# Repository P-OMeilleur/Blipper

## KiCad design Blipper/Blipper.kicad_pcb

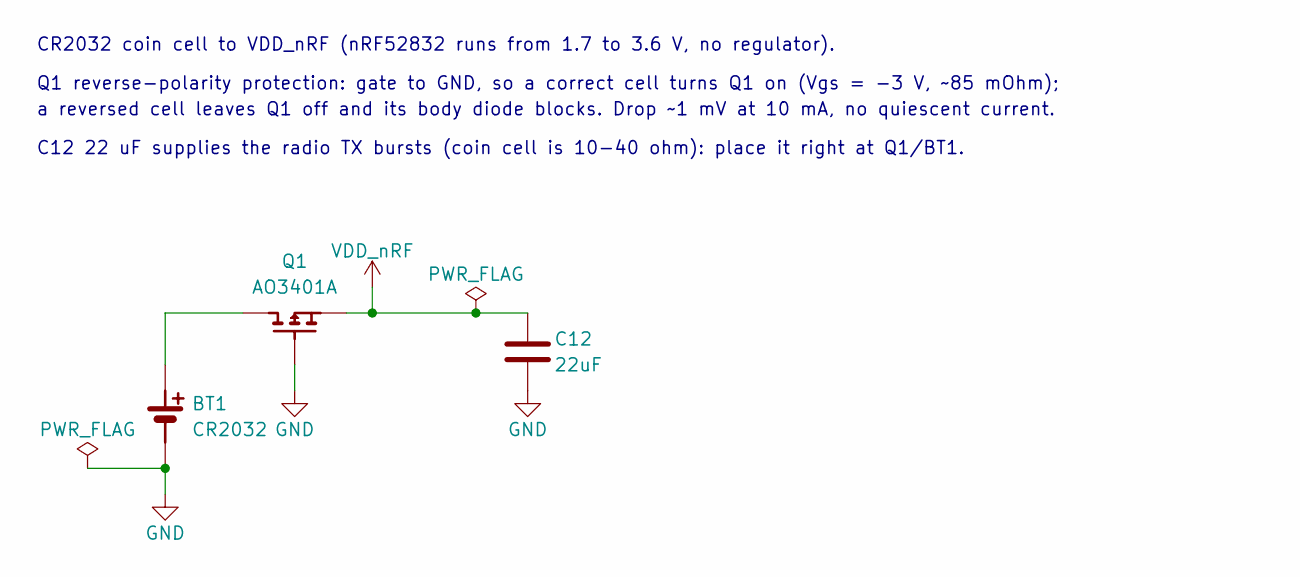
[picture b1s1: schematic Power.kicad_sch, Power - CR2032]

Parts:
BT1: CR2032; BatteryHolder_MYOUNG_MY-2032-16; MPN MY-2032-16; LCSC C2902340
C12: 22uF; C_0603_1608Metric; MPN CL10A226MQ8NRNC; LCSC C59461
Q1: AO3401A; SOT-23; MPN AO3401A; LCSC C15127

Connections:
GND: BT1.2 (-), C12.2, Q1.1 (G); also elsewhere on the board
unnamed: BT1.1 (+), Q1.3 (D)
VDD_nRF: C12.1, Q1.2 (S); also elsewhere on the board

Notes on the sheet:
C12 22 uF supplies the radio TX bursts (coin cell is 10-40 ohm): place it right at Q1/BT1.
Q1 reverse-polarity protection: gate to GND, so a correct cell turns Q1 on (Vgs = -3 V, ~85 mOhm);
CR2032 coin cell to VDD_nRF (nRF52832 runs from 1.7 to 3.6 V, no regulator).
a reversed cell leaves Q1 off and its body diode blocks. Drop ~1 mV at 10 mA, no quiescent current.

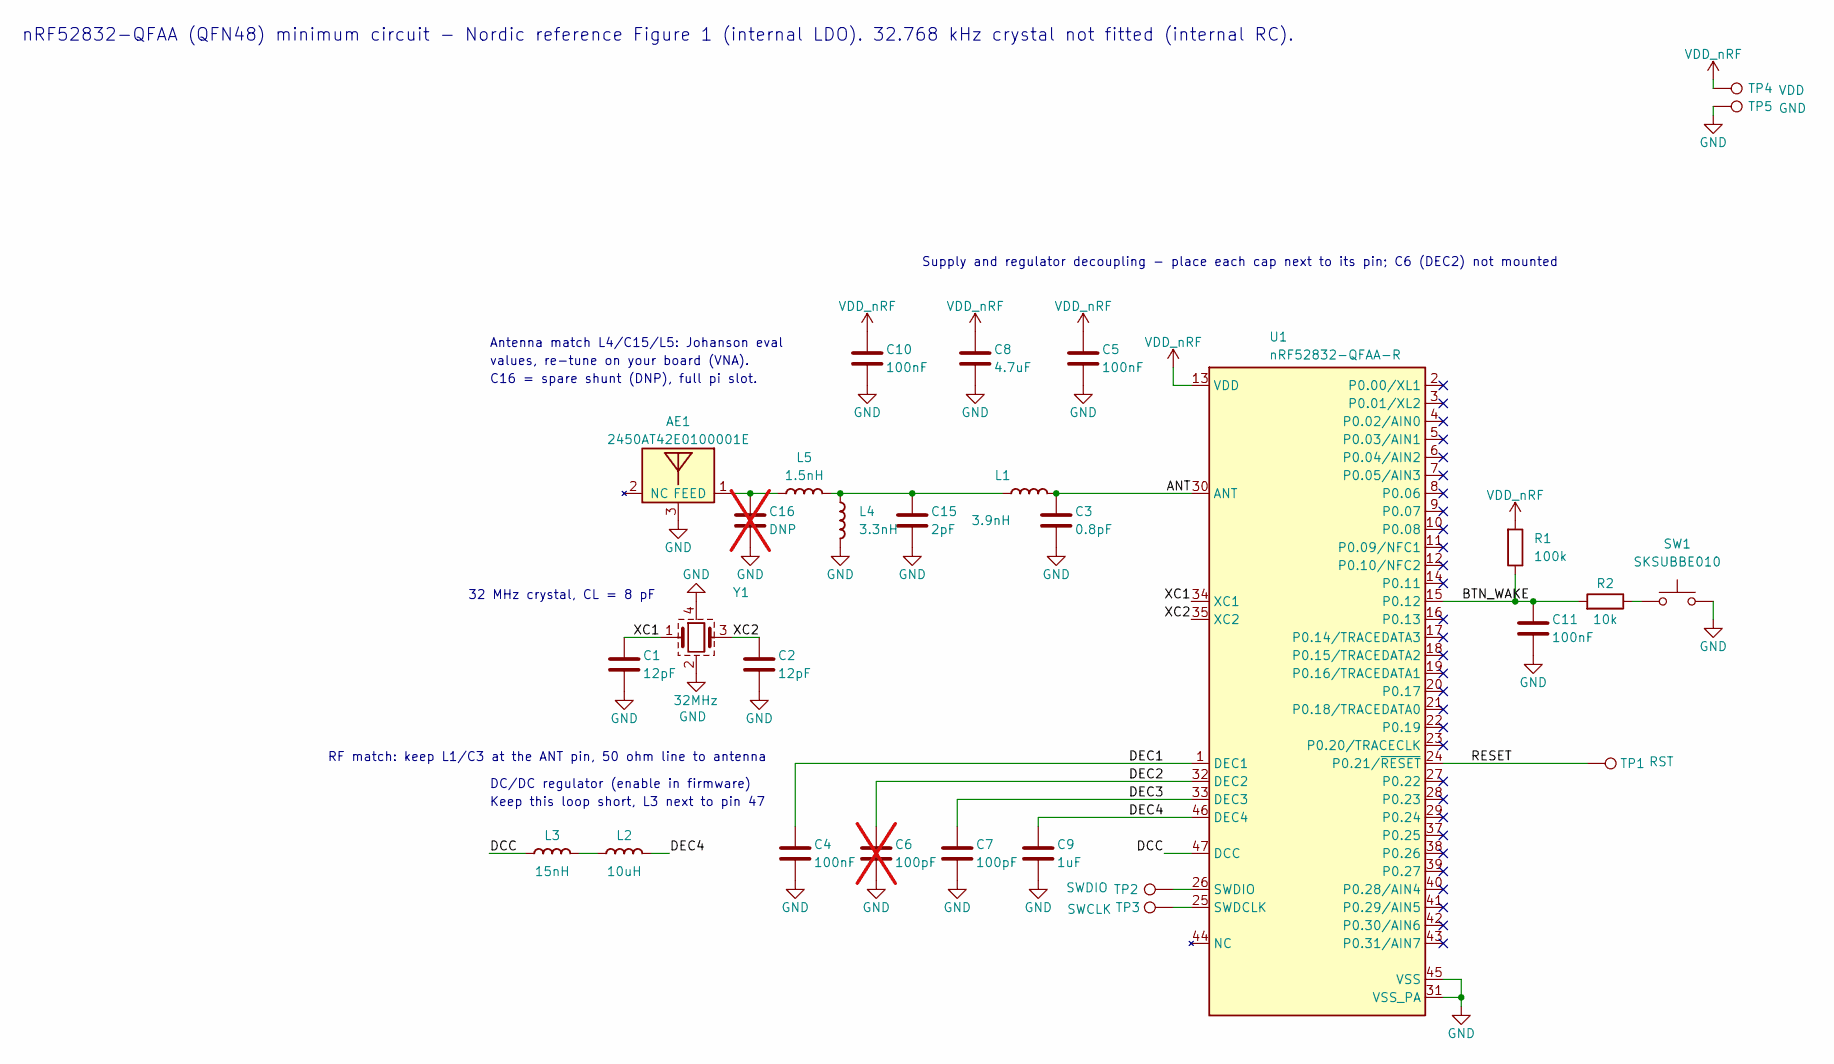
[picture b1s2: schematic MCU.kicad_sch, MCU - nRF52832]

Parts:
AE1: 2450AT42E0100001E; Antenna_Johanson_2450AT42E0100; MPN 2450AT42E0100001E; LCSC C17605137
C1, C2: 12pF; C_0402_1005Metric; MPN GRM1555C1H120GA01D; LCSC C161527
C3: 0.8pF; C_0402_1005Metric; MPN GJM1555C1HR80WB01D; LCSC C88902
C4, C5, C10, C11: 100nF; C_0402_1005Metric; MPN CL05B104KO5NNNC; LCSC C1525
C6: 100pF; C_0402_1005Metric; MPN 0402CG101J500NT; LCSC C1546; not fitted
C7: 100pF; C_0402_1005Metric; MPN 0402CG101J500NT; LCSC C1546
C8: 4.7uF; C_0603_1608Metric; MPN CL10A475KO8NNNC; LCSC C19666
C9: 1uF; C_0603_1608Metric; MPN CL10B105KA8NNNC; LCSC C29936
C15: 2pF; C_0402_1005Metric; MPN GJM1555C1H2R0BB01D; LCSC C161316
C16: DNP; C_0402_1005Metric; MPN GJM1555C1H2R0BB01D; LCSC C161316; not fitted
L1: 3.9nH; L_0402_1005Metric; MPN LQG15HS3N9S02D; LCSC C77109
L2: 10uH; L_0603_1608Metric; MPN MLZ1608M100WT000; LCSC C76798
L3: 15nH; L_0402_1005Metric; MPN VHF100505HQ15NJT; LCSC C395049
L4: 3.3nH; L_0402_1005Metric; MPN LQG15HS3N3S02D; LCSC C86064
L5: 1.5nH; L_0402_1005Metric; MPN LQG15HS1N5S02D; LCSC C77106
R1: 100k; R_0402_1005Metric; MPN 0402WGF1003TCE; LCSC C25741
R2: 10k; R_0402_1005Metric; MPN 0402WGF1002TCE; LCSC C25744
SW1: SKSUBBE010; SW_Alps_SKSU_5.4x5.3mm; MPN SKSUBBE010; LCSC C726003
TP1: RST; TestPoint_THTPad_D1.36mm_Drill1.0mm
TP2: SWDIO; TestPoint_THTPad_D1.36mm_Drill1.0mm
TP3: SWCLK; TestPoint_THTPad_D1.36mm_Drill1.0mm
TP4: VDD; TestPoint_THTPad_D1.36mm_Drill1.0mm
TP5: GND; TestPoint_THTPad_D1.36mm_Drill1.0mm
U1: nRF52832-QFAA-R; Nordic_QFN-48-1EP_6x6mm_P0.4mm_EP4.6x4.6mm
Y1: 32MHz; Crystal_SMD_2016-4Pin_2.0x1.6mm; MPN TX201632M4BBCE2T; LCSC C5339095

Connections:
/MCU/ANT: C3.1, L1.2, U1.30 (ANT)
/MCU/BTN_WAKE: C11.1, R1.2, R2.1, U1.15 (P0.12)
/MCU/DCC: L3.1, U1.47 (DCC)
/MCU/DEC1: C4.1, U1.1 (DEC1)
/MCU/DEC2: C6.1, U1.32 (DEC2)
/MCU/DEC3: C7.1, U1.33 (DEC3)
/MCU/DEC4: C9.1, L2.2, U1.46 (DEC4)
/MCU/RESET: TP1.1 (1_1), U1.24 (P0.21/~RESET)
/MCU/XC1: C1.1, U1.34 (XC1), Y1.1
/MCU/XC2: C2.1, U1.35 (XC2), Y1.3
GND: AE1.3, AE1.4, C1.2, C2.2, C3.2, C4.2, C5.2, C6.2, C7.2, C8.2, C9.2, C10.2, C11.2, C15.2, C16.2, L4.2, SW1.2, TP5.1 (1_1), U1.31 (VSS_PA), U1.45 (VSS), U1.49 (VSS), Y1.2 (GND), Y1.4 (GND); also elsewhere on the board
unnamed: AE1.1 (FEED_1), C16.1, L5.1
unnamed: C15.1, L1.1, L4.1, L5.2
unnamed: L2.1, L3.2
unnamed: R2.2, SW1.1
unnamed: TP3.1 (1_1), U1.25 (SWDCLK)
unnamed: TP2.1 (1_1), U1.26 (SWDIO)
VDD_nRF: C5.1, C8.1, C10.1, R1.1, TP4.1 (1_1), U1.13 (VDD), U1.36 (VDD), U1.48 (VDD); also elsewhere on the board

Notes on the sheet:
DC/DC regulator (enable in firmware)
32 MHz crystal, CL = 8 pF
C16 = spare shunt (DNP), full pi slot.
values, re-tune on your board (VNA).
nRF52832-QFAA (QFN48) minimum circuit - Nordic reference Figure 1 (internal LDO). 32.768 kHz crystal not fitted (internal RC).
Keep this loop short, L3 next to pin 47
Supply and regulator decoupling - place each cap next to its pin; C6 (DEC2) not mounted
Antenna match L4/C15/L5: Johanson eval
RF match: keep L1/C3 at the ANT pin, 50 ohm line to antenna

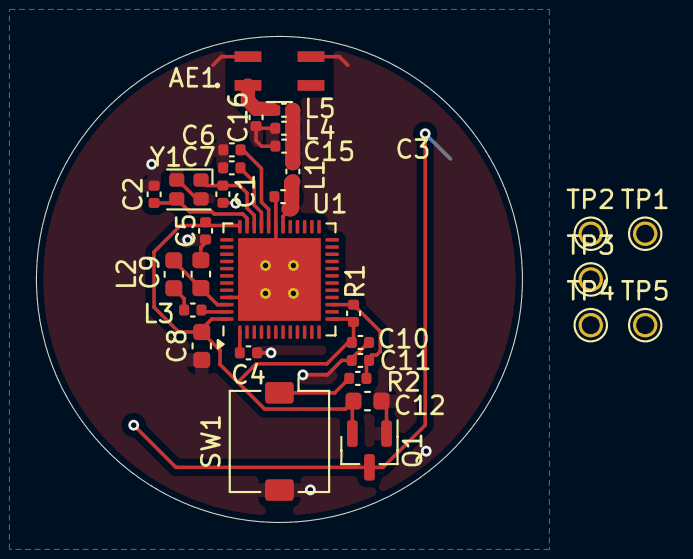
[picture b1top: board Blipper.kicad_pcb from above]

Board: 2 copper layers, 27.0 x 27.0 mm, 32 parts (1 on the bottom side), 19 nets.

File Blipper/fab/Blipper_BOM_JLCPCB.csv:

Comment,Designator,Footprint,LCSC Part #
2450AT42E0100001E,AE1,Antenna_Johanson_2450AT42E0100,C17605137
CR2032,BT1,BatteryHolder_MYOUNG_MY-2032-16,C2902340
12pF,"C1,C2",C_0402_1005Metric,C161527
0.8pF,C3,C_0402_1005Metric,C88902
100nF,"C4,C5,C10,C11",C_0402_1005Metric,C1525
100pF,C7,C_0402_1005Metric,C1546
4.7uF,C8,C_0603_1608Metric,C19666
1uF,C9,C_0603_1608Metric,C29936
22uF,C12,C_0603_1608Metric,C59461
2pF,C15,C_0402_1005Metric,C161316
3.9nH,L1,L_0402_1005Metric,C77109
10uH,L2,L_0603_1608Metric,C76798
15nH,L3,L_0402_1005Metric,C395049
3.3nH,L4,L_0402_1005Metric,C86064
1.5nH,L5,L_0402_1005Metric,C77106
AO3401A,Q1,SOT-23,C15127
100k,R1,R_0402_1005Metric,C25741
10k,R2,R_0402_1005Metric,C25744
SKSUBBE010,SW1,SW_Alps_SKSU_5.4x5.3mm,C726003
nRF52832-QFAA-R,U1,Nordic_QFN-48-1EP_6x6mm_P0.4mm_EP4.6x4.6mm,C77540
32MHz,Y1,Crystal_SMD_2016-4Pin_2.0x1.6mm,C5339095
